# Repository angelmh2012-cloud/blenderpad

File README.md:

# BlenderPad

BlenderPad is a custom macropad project built for Blender workflow shortcuts, gaming controls, and a small OLED mini game. It is designed to be programmable with CircuitPython and KMK firmware, making it easy to customize for different use cases.

## Project Overview
This project started as a beginner-friendly hardware and firmware build for HackClub. The goal is to create a compact keypad that can:
- trigger Blender shortcuts quickly
- switch between different key modes
- show the active mode on an OLED display
- support simple gaming-style input mappings

## What is included
This repository contains:
- a beginner-friendly 3D-printable case concept
- PCB design files
- firmware for the microcontroller
- a custom main script for mode switching and OLED output

## Hardware Features
The current design uses:
- an encoder for changing modes
- an OLED display for showing the active mode
- keys connected to GPIO pins for custom actions
- support for multiple functional profiles

## Firmware Details
The firmware is written in Python and uses KMK for keyboard behavior. The device supports:
- Blender shortcuts mode
- Friday Night Funkin mode
- a mini game mode displayed on the OLED screen

## Pin Layout
- SDA: D4
- SCL: D5
- Encoder: D1
- Keys: D7 to D10

## Software Requirements
The firmware relies on the following Python libraries:
- adafruit-circuitpython-ssd1306
- adafruit-circuitpython-busdevice
- adafruit-circuitpython-framebuf

## How to Use It
1. Flash CircuitPython onto the microcontroller.
2. Copy the firmware files and required libraries to the device.
3. Upload the main script.
4. Power the board and test the keys and encoder.

## Notes
This is a beginner project, so the design and firmware are still evolving. The main goal is to learn hardware programming, PCB design, and embedded firmware development in a fun and practical way.

## Future Ideas
Possible improvements include:
- adding more Blender shortcuts
- creating custom profiles for different programs
- improving the OLED mini game
- refining the case design for a cleaner final build

## Summary
BlenderPad is a fun, hands-on project that combines electronics, firmware, and creativity into one compact macropad. It is a great example of how small embedded projects can become useful tools for everyday tasks.

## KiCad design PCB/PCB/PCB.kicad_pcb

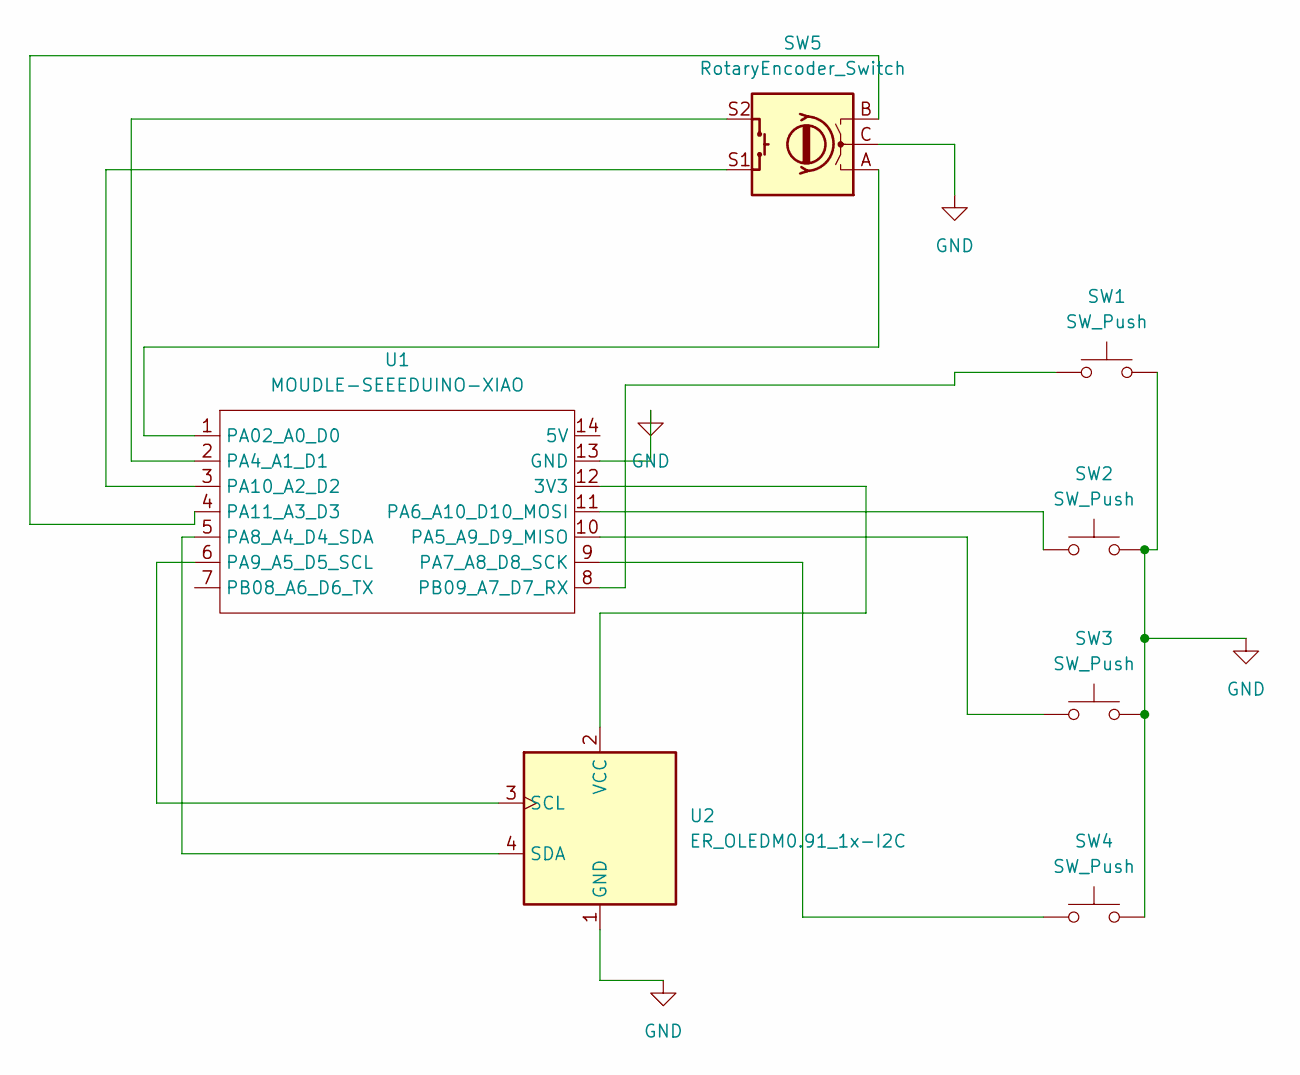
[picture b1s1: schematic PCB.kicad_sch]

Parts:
SW1, SW2, SW3, SW4: SW_Push; SW_Cherry_MX_1.00u_PCB
SW5: RotaryEncoder_Switch; RotaryEncoder_Alps_EC11E-Switch_Vertical_H20mm
U1: MOUDLE-SEEEDUINO-XIAO; XIAO-Generic-Hybrid-14P-2.54-21X17.8MM
U2: ER_OLEDM0.91_1x-I2C

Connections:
GND: SW1.2, SW2.2, SW3.2, SW4.2, SW5.C, U1.13 (GND), U2.1 (GND)
unnamed: U1.12 (3V3), U2.2 (VCC)
unnamed: SW5.A, U1.1 (PA02_A0_D0)
unnamed: SW5.S2, U1.2 (PA4_A1_D1)
unnamed: SW3.1, U1.10 (PA5_A9_D9_MISO)
unnamed: SW2.1, U1.11 (PA6_A10_D10_MOSI)
unnamed: SW4.1, U1.9 (PA7_A8_D8_SCK)
unnamed: U1.5 (PA8_A4_D4_SDA), U2.4 (SDA)
unnamed: U1.6 (PA9_A5_D5_SCL), U2.3 (SCL)
unnamed: SW5.S1, U1.3 (PA10_A2_D2)
unnamed: SW5.B, U1.4 (PA11_A3_D3)
unnamed: SW1.1, U1.8 (PB09_A7_D7_RX)

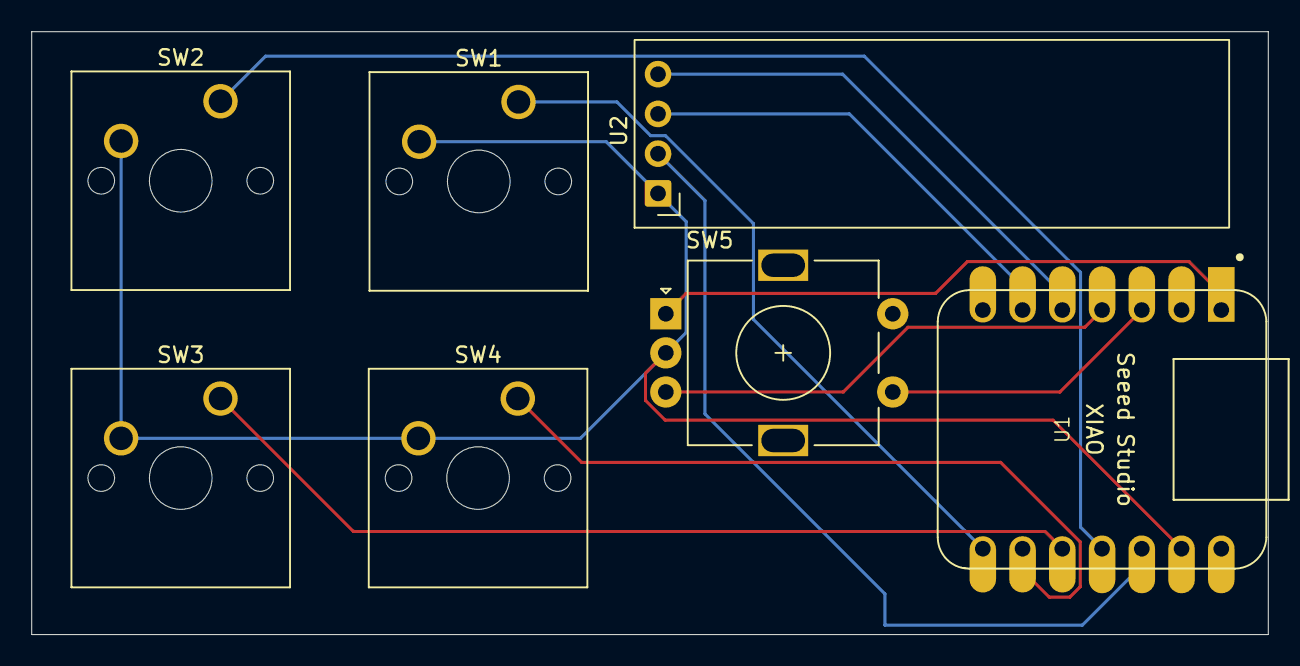
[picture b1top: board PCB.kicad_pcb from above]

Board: 2 copper layers, 79.0 x 38.5 mm, 7 parts (0 on the bottom side), 12 nets.
